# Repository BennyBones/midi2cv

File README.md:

# midi2cv v2 (modified from Elkayem's midi2cv design)

This is an modified version of Elkayem's midi2cv design. I have changed it from using banana jacks to 1/8" mono jacks and converted it to a pcb design better suited to eurorack format. A massive Thankyou to Elkayem for putting this code and project out there.

This repository contains the code and schematic for a DIY MIDI to CV converter.  I installed this converter into a home-built analog synthesizer, allowing me to play the synthesizer over MIDI.

The MIDI to CV converter includes the following outputs:

* Note CV output (88 keys, 1V/octave) using a 12-bit DAC
* Note priority (highest note, lowest note, or last note) selectable with jumper or 3-way switch
* Pitch bend CV output (0.5 +/-0.5V)
* Velocity CV output (0 to 4V)
* Control Change CV outout (0 to 4V)
* Trigger output (5V, 20 msec pulse for each new key played)
* Gate output (5V when any key depressed)
* Clock output (1 clock per quarter note, 20 msec 5V pulses)

## Parts
* Arduino Nano
* Optocoupler (I used a Vishay SFH618A, but there are plenty of alternatives out there)
* 2x MCP4822 12-bit DACs
* LM324N Quad Op Amp 
* Diode (e.g., 1N917)
* 2x 220, 500, 3x1K, 10K Ohm resistors
* 10K trim pot
* 3x 0.1 uF ceramic capacitors
* 5 pin MIDI jack
* 7x 1/4" (3.5mm) mono plug jacks
* 3-pin header or jumper (i used a JTS header)
* 3x 4-pin headers male and female
* 3-way switch SPDT
* 3mm LED
* 78L05

The Arduino code uses the standard MIDI and SPI libraries, which can be found in the Arduino Library Manager. 

The schematic is illustrated at the bottom of this page (Eagle file included).  Input power (VIN) is 9-12V.  This is required for the Note CV op amp, used for the 0-7.3V note output.  1% metal film resistors are recommended for the 10K resistors, for a constant op-amp gain that does not change with temperature. The 10k trim pot needs to be tuned to 7.7K between the center and inter leg.

The note priority options and jumper configuration are as follows:
* **Highest Note (+):** When multiple notes are sounded simultaneously, the highest note being held will be sounded.  When the highest note is released, the next highest note will be played, and so on.
* **Lowest Note (-):** Analagous to highest note, except the lowest note being held will be sounded. 
* **Last Note (L):** The most recent note played will be sounded.  When that note is released, the next most recent note still being held will be sounded.

I used Elkayem's schematic to build my first iteration on proto board, as he had. I 3-d printed a face panel and it worked pretty well.

I had a few problems with bad wires and cruddy solder joints, as well as a bad arduino which led me to converting the design to a pcb with a few changes. I removed the 7.7k (3k and 4.7K combined) resistors and replaced them with a 10k trim pot allowing some fine tuning if required. I also added an LED to the input to indicate whether the module was recieving signal or not.

I have added to this repository the gerber files for the PCBs so anyone can print them if they want them. I will also attach 3d model I did for my first design if anyone whats to use that also, note that the PCB and 3d printed face don't fit together.

Updates I have done to this PCB: 
* Fixed some alignment issues with the first version. 
* Made the MIDI jack hole the right size.
* Fixed the wiring for the LED.

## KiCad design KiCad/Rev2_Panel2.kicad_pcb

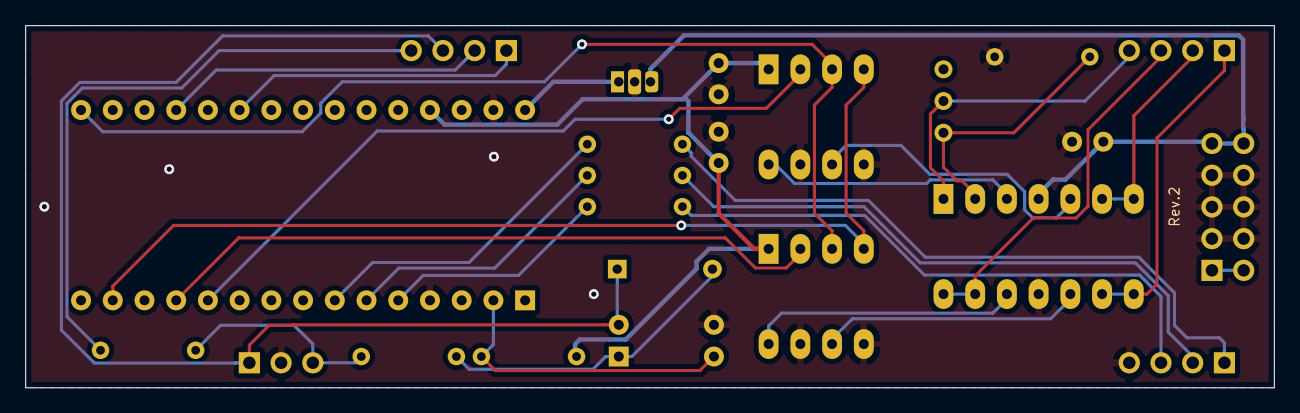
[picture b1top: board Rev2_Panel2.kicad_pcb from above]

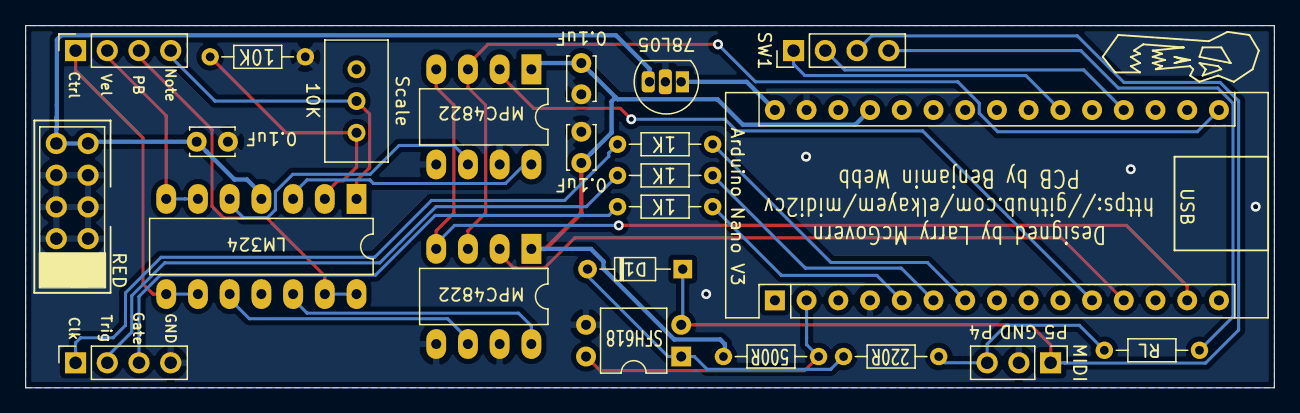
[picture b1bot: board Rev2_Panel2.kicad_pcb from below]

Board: 2 copper layers, 100.0 x 29.0 mm, 23 parts (23 on the bottom side), 31 nets.

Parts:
0.1uF, 0.1uF#2: 0.1uF; C_Disc_D3.4mm_W2.1mm_P2.50mm
1K, 1K#2, 1K#3: 1K; R_Axial_DIN0204_L3.6mm_D1.6mm_P7.62mm_Horizontal
10K: 10K; R_Axial_DIN0204_L3.6mm_D1.6mm_P7.62mm_Horizontal
78L05: L78L05_SO8; TO-92L_Inline
220R: 220R; R_Axial_DIN0204_L3.6mm_D1.6mm_P7.62mm_Horizontal
500R: 500R; R_Axial_DIN0204_L3.6mm_D1.6mm_P7.62mm_Horizontal
Arduino Nano V3: Arduino_Nano_v3.x; Arduino_Nano
C1: 0.1uF; C_Disc_D3.4mm_W2.1mm_P2.50mm
D1: DIODE; DiodeFlipped
LM324: LM324; DIP-14_W7.62mm_LongPads
MIDI: MidiDIN; PinHeader_1x03_P2.54mm_Vertical
MPC4822, MPC4822#2: MCP4822; DIP-8_W7.62mm_LongPads
Output1B1, Output2B1: Conn_01x04; PinSocket_1x04_P2.54mm_Vertical
RED: Conn_02x05_Top_Bottom; PinHeader_2x05_P2.54mm_Vertical
RL: 220R; R_Axial_DIN0204_L3.6mm_D1.6mm_P7.62mm_Horizontal
SFH618: SFH618A-2; DIP-4_W7.62mm
SW1: Conn_01x03; PinHeader_1x04_P2.54mm_Vertical
Scale: 10k; Potentiometer_Bourns_3296W_Vertical

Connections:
+5V: 0.1uF.2, 0.1uF#2.2, 500R.1, Arduino Nano V3.27, MPC4822.1, MPC4822#2.1
+12V: 78L05.3, C1.2, LM324.4, RED.9, RED.10
-12V: RED.1, RED.2
Clock: 1K#3.1, Output2B1.1
Control: LM324.8, LM324.9, Output1B1.1
GND: 0.1uF.1, 0.1uF#2.1, 10K.1, 78L05.2, Arduino Nano V3.4, Arduino Nano V3.29, C1.1, LM324.11, MIDI.2, MPC4822.5, MPC4822.7, MPC4822#2.5, MPC4822#2.7, Output2B1.4, RED.3, RED.4, RED.5, RED.6, RED.7, RED.8, SFH618.3
Gate: 1K.1, Output2B1.3
unnamed: 78L05.1, Arduino Nano V3.30
unnamed: 500R.2, Arduino Nano V3.2, SFH618.4
unnamed: 1K.2, Arduino Nano V3.5
unnamed: 1K#2.2, Arduino Nano V3.6
unnamed: 1K#3.2, Arduino Nano V3.7
unnamed: Arduino Nano V3.11, MPC4822#2.2
unnamed: Arduino Nano V3.12, MPC4822.2
unnamed: Arduino Nano V3.14, MPC4822.4, MPC4822#2.4
unnamed: Arduino Nano V3.16, MPC4822.3, MPC4822#2.3
unnamed: Arduino Nano V3.19, SW1.2
unnamed: Arduino Nano V3.21, SW1.1
unnamed: D1.1, MIDI.1, SFH618.2, SW1.3
unnamed: 220R.1, D1.2, SFH618.1
unnamed: LM324.5, MPC4822#2.6
unnamed: LM324.3, MPC4822#2.8
unnamed: LM324.10, MPC4822.6
unnamed: LM324.12, MPC4822.8
unnamed: 10K.2, LM324.2, Scale.1
unnamed: 220R.2, MIDI.3, RL.2
unnamed: RL.1, SW1.4
Note: LM324.1, Output1B1.4, Scale.2
PitchBend: LM324.13, LM324.14, Output1B1.3
Trigger: 1K#2.1, Output2B1.2
Velocity: LM324.6, LM324.7, Output1B1.2

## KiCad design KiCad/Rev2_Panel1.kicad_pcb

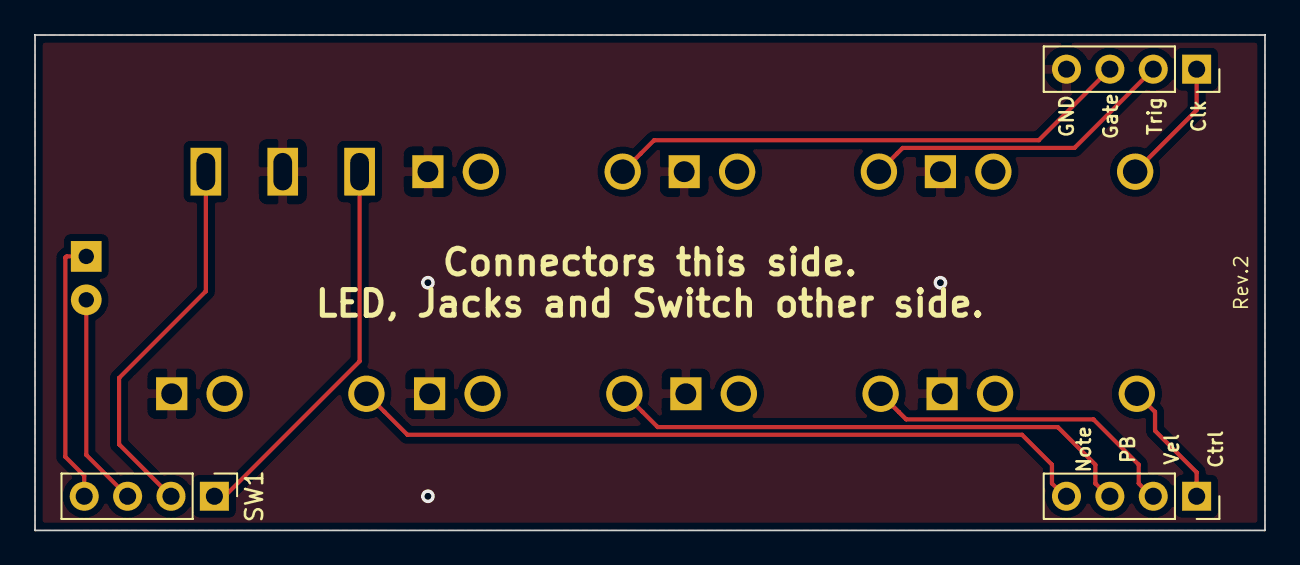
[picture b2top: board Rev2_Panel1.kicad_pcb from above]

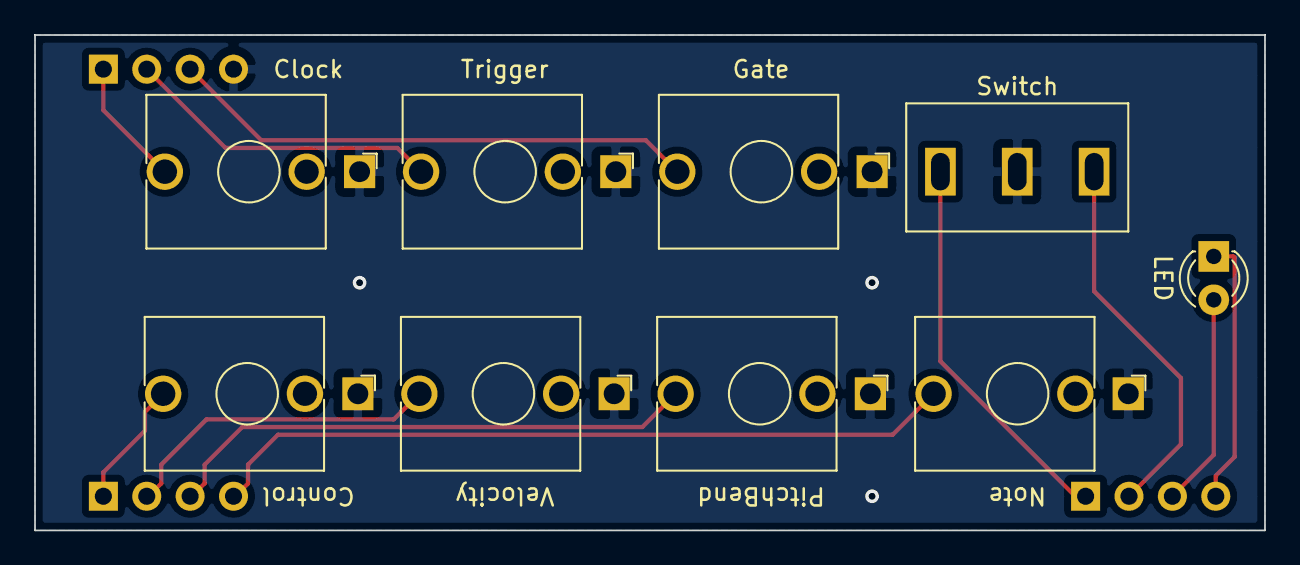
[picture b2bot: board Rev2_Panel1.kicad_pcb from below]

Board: 2 copper layers, 72.0 x 29.0 mm, 12 parts (9 on the bottom side), 12 nets.

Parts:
Clock: AudioJack2; Jack_3.5mm_QingPu_WQP-PJ398SM_Vertical_CircularHoles
Control: AudioJack2; Jack_3.5mm_QingPu_WQP-PJ398SM_Vertical_CircularHoles
Gate: AudioJack2; Jack_3.5mm_QingPu_WQP-PJ398SM_Vertical_CircularHoles
LED1: LED; LED_D3.0mm
Note: AudioJack2; Jack_3.5mm_QingPu_WQP-PJ398SM_Vertical_CircularHoles
Output1A1, Output2A1: Conn_01x04; PinSocket_1x04_P2.54mm_Vertical
PitchBend: AudioJack2; Jack_3.5mm_QingPu_WQP-PJ398SM_Vertical_CircularHoles
SW1: Conn_01x04; PinHeader_1x04_P2.54mm_Vertical
Switch: Switch; SPDT_3pin_switch
Trigger: AudioJack2; Jack_3.5mm_QingPu_WQP-PJ398SM_Vertical_CircularHoles
Velocity: AudioJack2; Jack_3.5mm_QingPu_WQP-PJ398SM_Vertical_CircularHoles

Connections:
GND: Clock.S, Control.S, Gate.S, Note.S, Output2A1.4, PitchBend.S, Switch.2, Trigger.S, Velocity.S
unnamed: Control.T, Output1A1.1
unnamed: Gate.T, Output2A1.3
unnamed: LED1.1, SW1.4
unnamed: LED1.2, SW1.3
unnamed: Note.T, Output1A1.4
unnamed: Output1A1.2, Velocity.T
unnamed: Output1A1.3, PitchBend.T
unnamed: Clock.T, Output2A1.1
unnamed: Output2A1.2, Trigger.T
unnamed: SW1.1, Switch.1
unnamed: SW1.2, Switch.3

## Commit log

2021-01-31 pcb update
2021-01-31 rearranged
